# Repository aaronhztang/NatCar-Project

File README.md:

# NatCar-Project

Demo URL: https://youtu.be/WA_4y2Vcu0U

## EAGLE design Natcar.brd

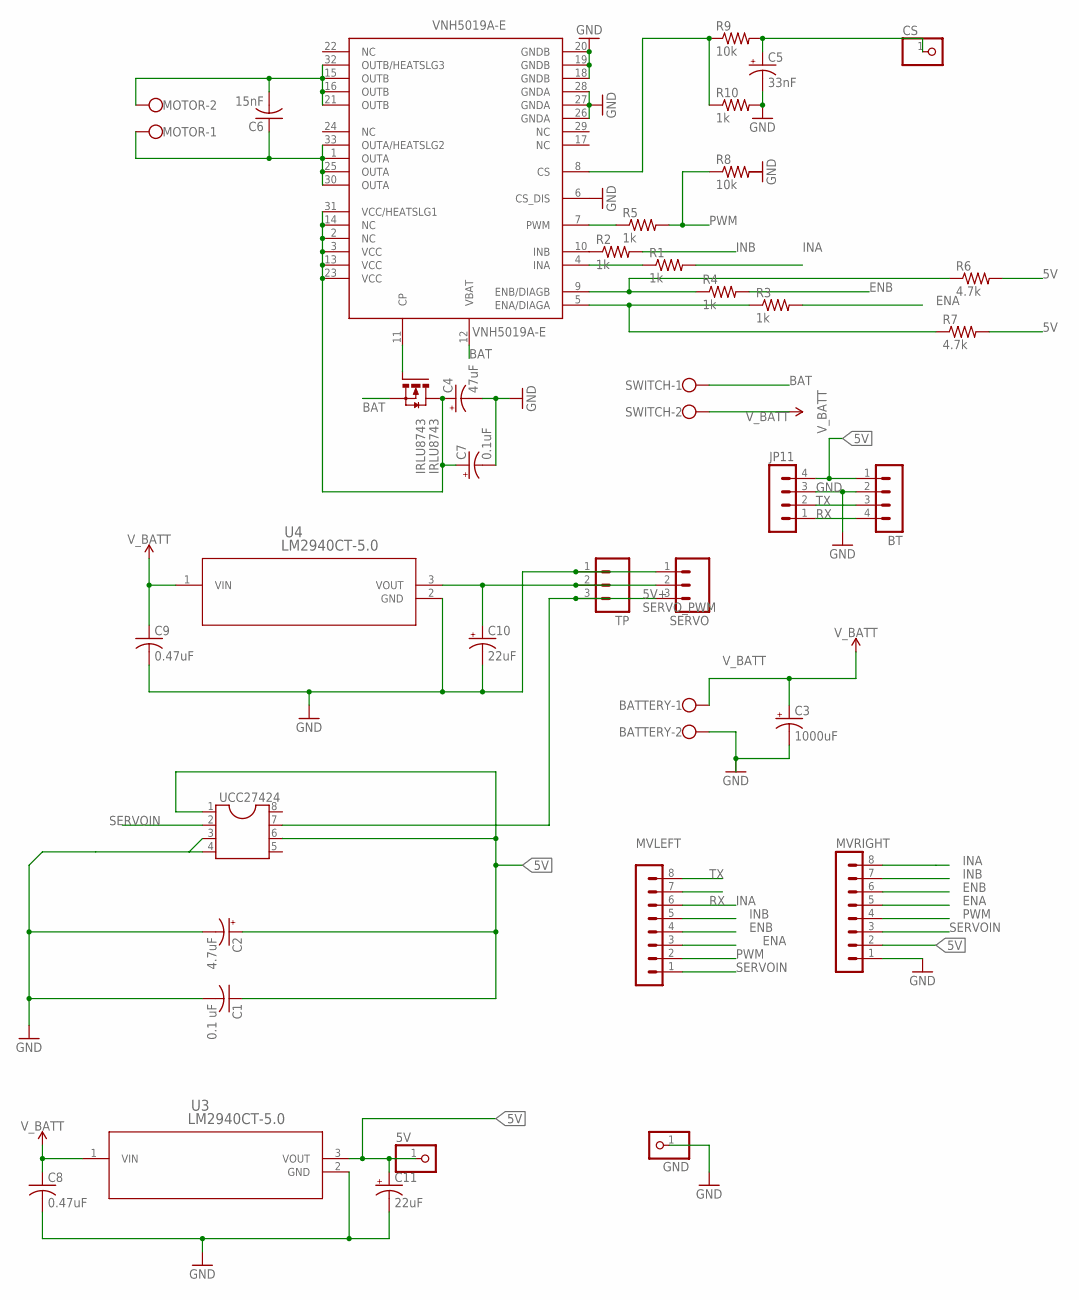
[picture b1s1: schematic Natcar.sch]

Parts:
5V: PINHD-1X1; 1X01
BATTERY: W237-102
BT: MA04-1
C1: 0.1 uF; C025-030X050
C2: 4.7uF; E2-5
C3: 1000uF; E5-10,5
C4: 47uF; E2,5-5
C5: 33nF; E2,5-5
C6: 15nF; C025-025X050
C7: 0.1uF; E2,5-5
C8, C9: 0.47uF; C025-030X050
C10, C11: 22uF; E2,5-5
CS: PINHD-1X1; 1X01
GND: PINHD-1X1; 1X01
IRLU8743: IRLU8743; TO251AA-V
JP11: MA04-1
MOTOR: W237-102
MVLEFT: MA08-1
MVRIGHT: MA08-1
R1, R2, R3, R4, R5, R10: 1k; 0207/7
R6, R7: 4.7k; 0207/7
R8, R9: 10k; 0207/7
SERVO: MA03; 03P
SWITCH: W237-102
TP: MA03; 03P
U3, U4: LM2940CT-5.0; T03B
UCC27424: DIL8S; SOCKET-08
VNH5019A-E: VNH5019A-E; MULTIPOWERSO-30

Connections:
5V: 5V.1, BT.1, C1.1, C2.+, C11.+, JP11.4, MVRIGHT.2, R6.2, R7.2, U3.3 (VOUT), UCC27424.1, UCC27424.6
5V+: C10.+, SERVO.2, TP.2, U4.3 (VOUT)
BAT: IRLU8743.3 (S), SWITCH.1, VNH5019A-E.12 (VBAT)
ENA: MVLEFT.3, MVRIGHT.5, R3.2
ENB: MVLEFT.4, MVRIGHT.6, R4.2
GND: BATTERY.2, BT.2, C1.2, C2.-, C3.-, C4.-, C5.-, C7.-, C8.2, C9.2, C10.-, C11.-, GND.1, JP11.3, MVRIGHT.1, R10.2, SERVO.1, TP.1, U3.2 (GND), U4.2 (GND), UCC27424.3, UCC27424.4, VNH5019A-E.6 (CS_DIS), VNH5019A-E.18 (GNDB), VNH5019A-E.19 (GNDB), VNH5019A-E.20 (GNDB), VNH5019A-E.26 (GNDA), VNH5019A-E.27 (GNDA), VNH5019A-E.28 (GNDA)
INA: MVLEFT.6, MVRIGHT.8, R1.2
INB: MVLEFT.5, MVRIGHT.7, R2.2
unnamed: R9.1, R10.1, VNH5019A-E.8 (CS)
unnamed: R1.1, VNH5019A-E.4 (INA)
unnamed: R2.1, VNH5019A-E.10 (INB)
unnamed: R3.1, R7.1, VNH5019A-E.5 (ENA/DIAGA)
unnamed: R4.1, R6.1, VNH5019A-E.9 (ENB/DIAGB)
unnamed: R5.1, VNH5019A-E.7 (PWM)
unnamed: C5.+, CS.1, R9.2
unnamed: IRLU8743.1 (G), VNH5019A-E.11 (CP)
OUTA: C6.1, MOTOR.1, VNH5019A-E.1 (OUTA), VNH5019A-E.25 (OUTA), VNH5019A-E.30 (OUTA), VNH5019A-E.33 (OUTA/HEATSLG2)
OUTB: C6.2, MOTOR.2, VNH5019A-E.15 (OUTB), VNH5019A-E.16 (OUTB), VNH5019A-E.21 (OUTB), VNH5019A-E.32 (OUTB/HEATSLG3)
PWM: MVLEFT.2, MVRIGHT.4, R5.2, R8.1
RX: BT.4, JP11.1, MVLEFT.7
SERVOIN: MVLEFT.1, MVRIGHT.3, UCC27424.2
SERVO_PWM: SERVO.3, TP.3, UCC27424.7
TX: BT.3, JP11.2, MVLEFT.8
VCC: C4.+, C7.+, IRLU8743.2 (D), VNH5019A-E.2 (NC), VNH5019A-E.3 (VCC), VNH5019A-E.13 (VCC), VNH5019A-E.14 (NC), VNH5019A-E.23 (VCC), VNH5019A-E.31 (VCC/HEATSLG1)
V_BATT: BATTERY.1, C3.+, C8.1, C9.1, SWITCH.2, U3.1 (VIN), U4.1 (VIN)

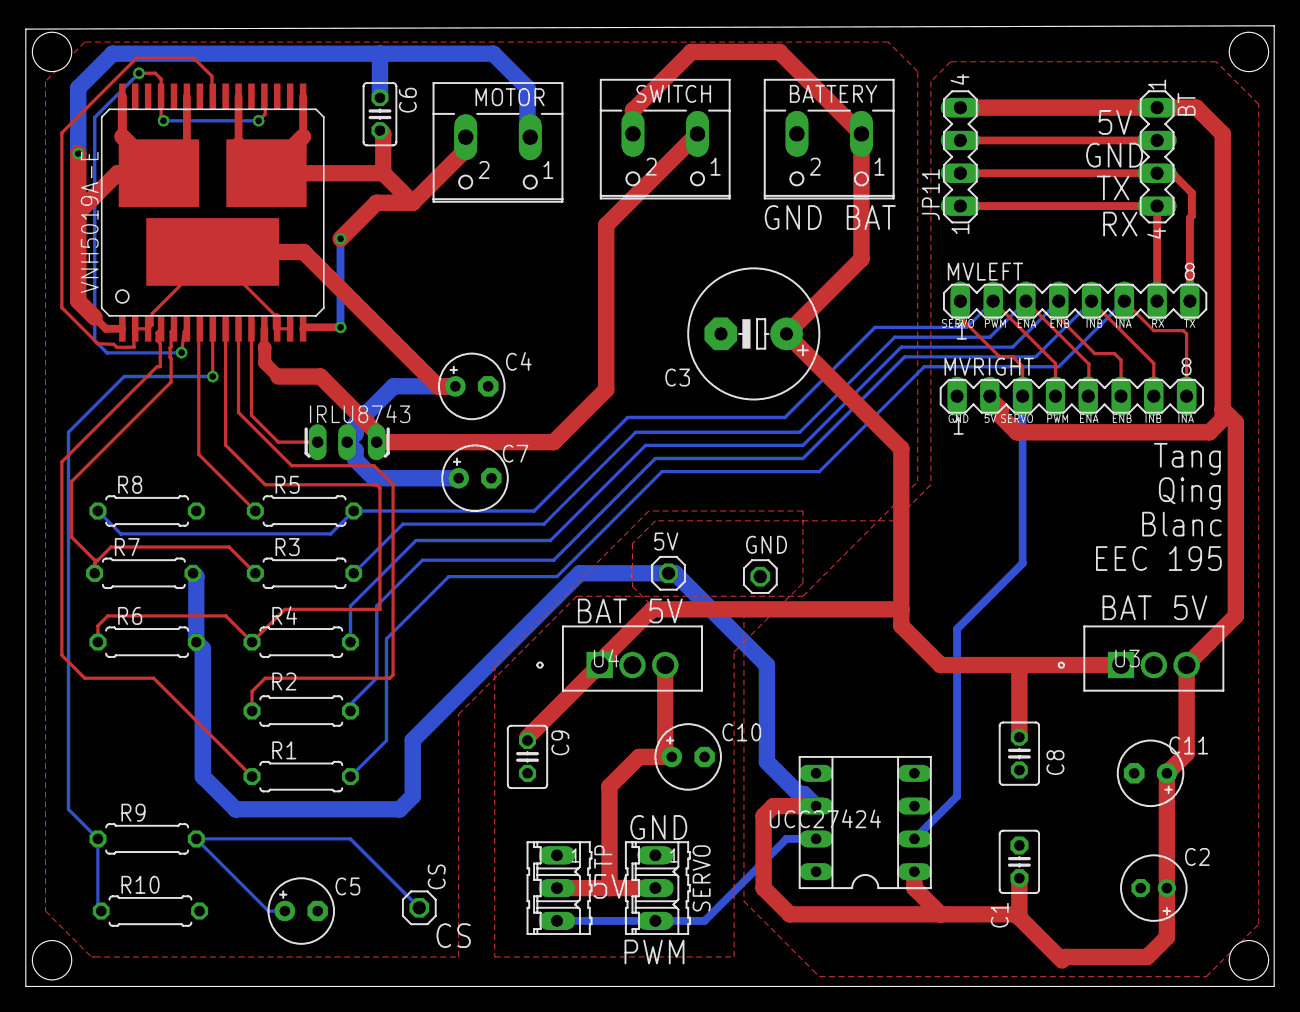
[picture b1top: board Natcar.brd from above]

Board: 2 copper layers, 96.7 x 74.4 mm, 38 parts (0 on the bottom side), 25 nets.

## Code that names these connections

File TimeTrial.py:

#*****************************************************************************
#
# Application Name     -   EEC195B Time Trial
# Application Overview -   Natcar Time Trial
# Author               -   Huangze Tang, Eric Qing, Ryan Blanc
#
#*****************************************************************************

import sensor, image, time, math, pyb
import utime
from pyb import LED, UART, Pin, Timer

# Always pass UART 1 for the UART number for your OpenMV Cam.
# The second argument is the UART baud rate. For a more advanced UART control
# example see the BLE-Shield driver.
uart = UART(1, 115200, timeout_char=1000)

# Initialize the command.
command = '0'

# Color Tracking Thresholds (Grayscale Min, Grayscale Max)
# The below grayscale threshold is set to only find extremely bright white areas.
thresholds = (250, 255)

# Each roi is (x, y, w, h).
# This roi spans the entire width of the image and is about 10 pixels high, which is in the top-portion of the image.
roi = (0, 0, 160, 10)

# Initialize the position variable.
angle = 0
# Store the error buffer for the PID caculation.
prev_e_1 = 0
prev_e_2 = 0
prev_e_3 = 0
prev_e_4 = 0
# Initialize the PID term.
Pterm = 0
Dterm = 0
Iterm = 0
prev_I = 0

# Camera setup...
sensor.reset() # Initialize the camera sensor.
sensor.set_pixformat(sensor.GRAYSCALE) # use grayscale.
sensor.set_framesize(sensor.QQVGA) # use QQVGA for speed. (160*120)
sensor.skip_frames(time = 2000) # Let new settings take affect.
sensor.set_auto_gain(False) # must be turned off for color tracking
sensor.set_auto_whitebal(False) # must be turned off for color tracking
clock = time.clock() # Tracks FPS.
led = LED(1) # Initialize the red LED.
led.off() # Turn off the red LED.
i = 0 # Initialize the counter

# Initialize the control signals for the VNH5019A-E.
ina = pyb.Pin("P2", pyb.Pin.OUT_PP) # Initialize the ina.
ina.high() # Turn on the pin.
inb = pyb.Pin("P3", pyb.Pin.OUT_PP) # Initialize the inb.
inb.low() # Turn off the pin.
ena = pyb.Pin("P6", pyb.Pin.OUT_PP) # Initialize the ena.
ena.high() # Turn on the pin.
enb = pyb.Pin("P5", pyb.Pin.OUT_PP) # Initialize the enb.
enb.high() # Turn on the pin.


stop = True # Initialize the stop flag.
stopcounter = 0 # Initialize the final line flag.
finish = LED(2) # Initialize the green LED for finishing.
finish.off() # Turn off the green LED.
start = 0 # Initialize the start time.
delta = 0 # Initialize the program time.
start = utime.ticks_ms() # Record the start time.

# Set up two Timers for servo and motor at different frequencies.
tim1 = Timer(4, freq=300)
# Frequency in Hz for the digital servo.
tim2 = Timer(2, freq=1000)
# Frequency in Hz for the DC Motor.

# Initialize the desired pulse width in seconds (1.5ms).
DPW = 0.0015
Timescaler = tim1.source_freq() / (tim1.prescaler() + 1)
# Calculate the actual pulse width based on the source frequency and the prescale value in OpenMV.
APW = DPW * Timescaler

# Generate a PWM square wave on TIM4 with calculated actual pulse width on channel 1.
ch1 = tim1.channel(1, Timer.PWM, pin=Pin("P7"), pulse_width=int(APW))
# Generate a PWM square wave on TIM2 with 0 pulse width percent on channel 3.
ch3 = tim2.channel(3, Timer.PWM, pin=Pin("P4"), pulse_width_percent=0)

# Set up the PID Value.
Ku = 4
Pu = 10
Kp = Ku/1.7
Kd = Kp*Pu/2
Ki = 0

# Only blobs that with more pixels than "pixel_threshold" and more area than "area_threshold" are
# returned by "find_blobs" below. Change "pixels_threshold" and "area_threshold" if you change the
# camera resolution. "merge=True" merges all overlapping blobs in the image.

while(True):
    clock.tick() # Track elapsed milliseconds between snapshots().
    # BT Control.
    if uart.any() > 0 :
        # Read a single character frm UART1.
        command = chr(uart.readchar())
        # Print the command.
        print (command)
        # "g" for start, "s" for stop.
        if command == 'g' :
            stop = False
            finish.off()
        elif command == 's' :
            stop = True
            finish.on()
            ch3.pulse_width_percent(0)

    # Run the car front when stop is false.
    if stop == False :
        ina.high()
        inb.low()

    img = sensor.snapshot() # Take a picture and return the image.

    # Find blobs in the top-portion in the image.
    blobs = img.find_blobs([thresholds], roi=roi, pixels_threshold=5, area_threshold=10, merge=True)

    # If there is any blob in the top-portion:
    if (len(blobs) >= 1):
        # Find the blob closest to the previous center.
        center_blob = min(blobs, key=lambda b: math.sqrt(pow((b.cx() - 80 + prev_e_1),2) + pow((b.cy() - 5),2)))
        # Draw a rect around the blob.
        img.draw_rectangle(center_blob.rect(), color = 0)
        # Draw a cross through the center's coordinate.
        img.draw_cross(center_blob.cx(), center_blob.cy(), color = 0)
        # Replace the center x position.
        
        # Refresh the error buffer.
        prev_e_4 = prev_e_3
        prev_e_3 = prev_e_2
        prev_e_2 = prev_e_1
        # To decrease the oscillation, refresh the newest error only when 
        # the newest one has enough difference from the previous one.
        if math.fabs(prev_e_1 - 80 + center_blob.cx()) > 10:
            prev_e_1 = 80 - center_blob.cx()

        # Refresh the Iterm.
        prev_I = Iterm

        # Refresh the PID term.
        Pterm = prev_e_1
        Dterm = (prev_e_1 - prev_e_3 + 3*prev_e_1 - 3*prev_e_2)/(6*0.0125)
        Iterm = prev_I + 0.0125 * (prev_e_1 + prev_e_2) / 2

        # Calculate the current error for the correction.
        current_error = Kp * Pterm + Kd * Dterm + Ki * Iterm

        # Neglect the I Term to "unwind".
        if current_error > 100 or current_error < -100:
            current_error = Kp * Pterm + Kd * Dterm
        # Set up the deadband to decrease the sensibility.
        if current_error > 30 or current_error < -30:
        	# Calculate the angle based on the current error.
            angle = math.degrees(math.atan(current_error/120)) + 90
        else :
            angle = 90

        print("Turn Angle: %f" % angle)
        # Calculate the deflection angle away from the straight way.
        Deflection = math.fabs(angle - 90)
        # Calculate the desired pulse width based on the angle the car should go.
        DPW = ((angle/180.0) + 1.0) * 0.001
        # Transform the desired pulse width into the actual one.
        APW = DPW * Timescaler
        # Adjust the pulse width for the servo.
        ch1.pulse_width(int(APW))
        # Calculate the time from starting.
        delta = utime.ticks_diff(utime.ticks_ms(), start)
        # When the program has started 10s and detects three blobs in front.
        if delta > 10000 and len(blobs) == 3 :
        	# To tell from the finish line and the crossover.
            if (blobs[0].w() <= 15 and blobs[1].w() <= 15 and blobs[2].w() <= 15) :
                # Turn on the finish LED.
                finish.on()
                # Detect the line.
                stopcounter = 1

        # If stopcounter or stop flag is high, stop the car.      
        # Adjust the pulse width percent for the motor based on the deflection angle.
        # When the deflection angle is small, the motor should spin fast.
        # But the deflection angle is large, the motor should slow down.
        if stopcounter == 1 :
        	# Reverse the car to stop the car  in the desired range.
            ina.low()
            inb.high()
            ch3.pulse_width_percent(30)
            stopcounter = 0
            stop = True
            time.sleep(400)
        elif stop == True:
            ch3.pulse_width_percent(0)
        elif Deflection < 20 :
            ch3.pulse_width_percent(50)
        elif Deflection < 40 :
            ch3.pulse_width_percent(40)
        elif Deflection < 60 :
            ch3.pulse_width_percent(25)
        else :
            ch3.pulse_width_percent(25)

    # Measure the frame rate and print it.
    print(clock.fps())

    # When the main loops 20 times, toggle the red LED.
    if i == 20 :
        led.toggle() # LED toggle.
        i = 0 # Reset the counter.
    i = i + 1 # Increase the counter.

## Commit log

2020-12-21 Final Demo
2020-12-21 Update Demo URL

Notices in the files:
parts and their libraries:
SparkFun-PowerSymbols: Licensing: Creative Commons ShareAlike 4.0 International - https://creativecommons.org/licenses/by-sa/4.0
